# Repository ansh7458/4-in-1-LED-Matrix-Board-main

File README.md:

# 🎮 4-in-1 LED Matrix Board

> **Centre for Electronic Design and Technology**  
> Netaji Subhas University of Technology, New Delhi  
> *Date: December 2024*

---

## 📋 Table of Contents
- [Synopsis](#-synopsis)
- [Introduction](#-introduction)
- [System Overview](#-system-overview)
- [Working Modes](#-working-modes)
- [Program Logic](#-program-logic)
- [Inputs & Control](#-inputs--control)
- [Bill of Materials](#-bill-of-materials)

---

## 🎯 Synopsis

A compact and multifunctional **5×7 LED dot matrix system** built around an **Arduino Nano**. It integrates **four interactive modules** into a single educational platform:

- 🔤 **Morse Tutor** — Learn Morse code interactively
- ⏳ **LED Hourglass** — Tilt-controlled sand animation
- 👁️ **Persistence of Vision (POV) Demo** — Visual persistence effect
- 🌡️ **Temperature Display** — Real-time thermistor reading

User interaction is achieved via **buttons**, **tilt switches**, and a **potentiometer**. The system leverages **Timer1 CTC interrupts** for flicker-free LED multiplexing.

## 📖 Introduction

LED matrices are widely used in educational and commercial applications. This project creates a single, compact platform that consolidates multiple mini-projects, enabling learners to explore different aspects of embedded system design:

| Mode | Concept Demonstrated |
|------|---------------------|
| Morse Tutor | Digital output control, timing-based signal generation |
| Hourglass | Tilt-sensor input handling, animation sequencing |
| POV Demo | Persistence-of-vision, real-time potentiometer control |
| Temperature | Analog sensor reading, calculation, text rendering |

## 🔧 System Overview

### Block Diagram

### Pin Assignment (Arduino Nano)

| Pin | Signal | Connected To | Function |
|-----|--------|-------------|----------|
| D2-D8 | R1-R7 | ULN2003 | Row drives for LED matrix |
| D9-D13 | C1-C5 | BC327 transistors | Column drives |
| A1-A3 | BTN1-3 | Push Buttons | Navigation (Next/Prev/Select) |
| A4-A5 | Tilt 1-2 | Tilt Switches | Hourglass orientation |
| A6 | Thermistor | NTC | Temperature sensing |
| A7 | Pot | RV1 | POV speed control |

## 🎮 Working Modes

### 1. 🏠 Home Screen
Menu navigation using three push buttons (Next, Previous, Select). Long press (~5s) on Button 1 returns to home from any mode.

### 2. 🔤 Morse Tutor
Displays Morse code patterns for A–Z on the LED matrix with timing-based dot/dash rendering.

### 3. ⏳ Hourglass
Tilt-controlled sand animation with direction detection. Passive buzzer alerts when timer completes.

### 4. 👁️ POV Demo
Potentiometer controls Timer1 compare register, varying refresh frequency to demonstrate persistence-of-vision effect.

### 5. 🌡️ Temperature Display
NTC thermistor with **Beta parameter model** for temperature calculation, displayed as scrolling digits on the matrix.

## ⚙️ Program Logic

The firmware follows a **cooperative architecture**:
- **Foreground (main loop)**: User input processing, mode logic, display buffer updates
- **Background (Timer1 ISR)**: Column-wise LED multiplexing at high speed for flicker-free display

## 📦 Bill of Materials

| S.No | Component | Value | Qty |
|------|-----------|-------|-----|
| 1 | Arduino Nano | — | 1 |
| 2 | 5×7 LED Matrix | — | 1 |
| 3 | ULN2003 | Darlington Array | 1 |
| 4 | BC327 | PNP Transistor | 5 |
| 5 | Push Buttons | — | 3 |
| 6 | Tilt Switches | — | 2 |
| 7 | NTC Thermistor | 10 kΩ | 1 |
| 8 | Potentiometer | — | 1 |
| 9 | Passive Buzzer | — | 1 |

## 🛠️ Technologies Used

`Arduino (C/C++)` · `KiCad` · `Timer Interrupts (CTC)` · `Embedded Systems` · `PCB Design`

## 👥 Author
- **Ansh Gupta** — NSUT, New Delhi

---
*Centre for Electronic Design and Technology, NSUT, New Delhi*

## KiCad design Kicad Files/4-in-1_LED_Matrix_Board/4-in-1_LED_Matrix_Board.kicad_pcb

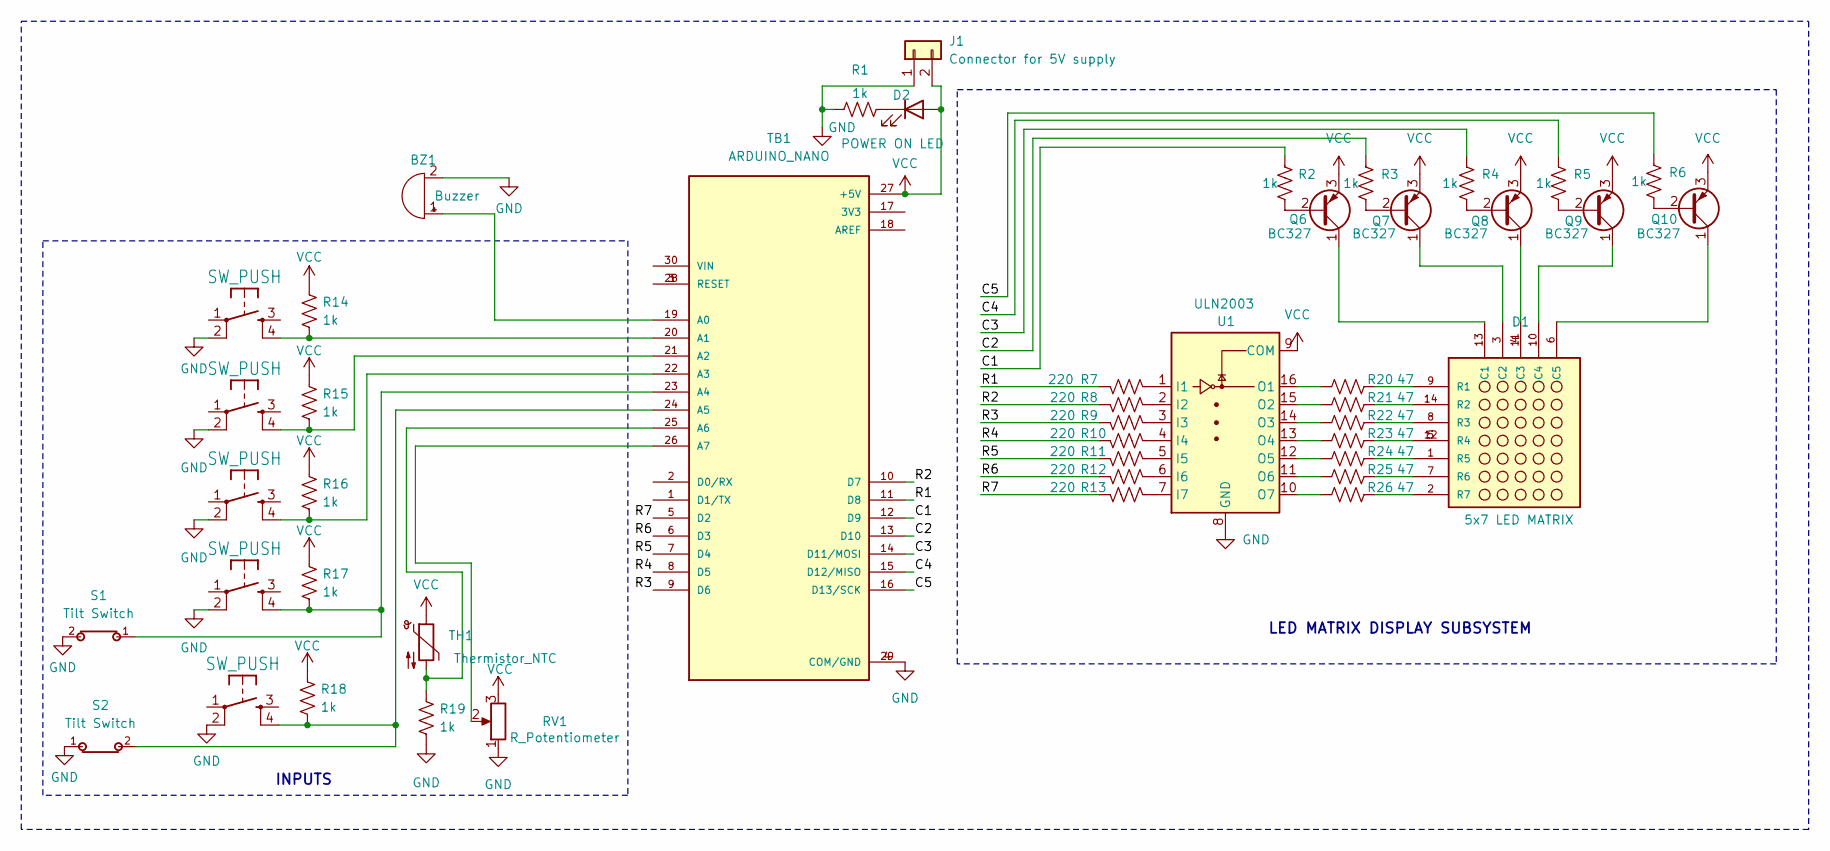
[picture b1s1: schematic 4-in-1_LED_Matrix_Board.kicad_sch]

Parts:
BZ1: Buzzer; XDCR_AT-1438-TWT-R
D1: 5x7 LED MATRIX; LED_TA20-11SRWA; PARTREV V.1A
D2: POWER ON LED; LED_D3.0mm
J1: Connector for 5V supply; JST_EH_B2B-EH-A_1x02_P2.50mm_Vertical
Q6, Q7, Q8, Q9, Q10: BC327; TO-92L_Inline_Wide
R1, R14, R15, R16, R17, R18, R19: 1k; R_Axial_DIN0204_L3.6mm_D1.6mm_P7.62mm_Horizontal
R2, R3, R4, R5, R6: 1k; R_Axial_DIN0207_L6.3mm_D2.5mm_P10.16mm_Horizontal
R7, R8, R9, R10, R11, R12, R13: 220; R_Axial_DIN0204_L3.6mm_D1.6mm_P7.62mm_Horizontal
R20, R21, R22, R23, R24, R25, R26: 47; R_Axial_DIN0204_L3.6mm_D1.6mm_P7.62mm_Horizontal
RV1: R_Potentiometer; RJ9W_2
S1, S2: Tilt Switch; SW-520D
SW1, SW2, SW3, SW4, SW5: SW_PUSH; B3F-40XX
TB1: ARDUINO_NANO; SHIELD_ARDUINO_NANO
TH1: Thermistor_NTC; THERM_GA50K6A1A
U1: ULN2003; DIP-16_W7.62mm

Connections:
/C1: R2.2, TB1.12 (D9)
/C2: R3.1, TB1.13 (D10)
/C3: R4.1, TB1.14 (D11/MOSI)
/C4: R5.1, TB1.15 (D12/MISO)
/C5: R6.1, TB1.16 (D13/SCK)
/R1: R7.1, TB1.11 (D8)
/R2: R8.1, TB1.10 (D7)
/R3: R9.1, TB1.9 (D6)
/R4: R10.1, TB1.8 (D5)
/R5: R11.1, TB1.7 (D4)
/R6: R12.1, TB1.6 (D3)
/R7: R13.1, TB1.5 (D2)
GND: BZ1.2 (-), J1.1, R1.1, R19.1, RV1.1, S1.2, S2.1, SW1.2 (P1), SW2.2 (P1), SW3.2 (P1), SW4.2 (P1), SW5.2 (P1), TB1.4 (COM/GND), TB1.29 (COM/GND), U1.8 (GND)
unnamed: BZ1.1 (+), TB1.19 (A0)
unnamed: D1.13 (C1), Q6.1 (C)
unnamed: D1.3 (C2), Q7.1 (C)
unnamed: D1.10 (C4), Q9.1 (C)
unnamed: D1.6 (C5), Q10.1 (C)
unnamed: D1.9 (R1), R20.1
unnamed: D1.14 (R2), R21.1
unnamed: D1.8 (R3), R22.1
unnamed: D1.5 (R4), D1.12 (R4), R23.1
unnamed: D1.1 (R5), R24.1
unnamed: D1.7 (R6), R25.1
unnamed: D1.2 (R7), R26.1
unnamed: D2.1 (K), R1.2
unnamed: Q6.2 (B), R2.1
unnamed: Q7.2 (B), R3.2
unnamed: Q8.2 (B), R4.2
unnamed: D1.4 (C3), D1.11 (C3), Q8.1 (C)
unnamed: Q9.2 (B), R5.2
unnamed: Q10.2 (B), R6.2
unnamed: R14.1, SW1.4 (S1), TB1.20 (A1)
unnamed: R15.1, SW2.4 (S1), TB1.21 (A2)
unnamed: R16.1, SW3.4 (S1), TB1.22 (A3)
unnamed: R17.1, S1.1, SW4.4 (S1), TB1.23 (A4)
unnamed: R18.1, S2.2, SW5.4 (S1), TB1.24 (A5)
unnamed: R19.2, TB1.25 (A6), TH1.2
unnamed: RV1.2, TB1.26 (A7)
unnamed: TB1.3 (RESET), TB1.28 (RESET)
unnamed: R7.2, U1.1 (I1)
unnamed: R8.2, U1.2 (I2)
unnamed: R9.2, U1.3 (I3)
unnamed: R10.2, U1.4 (I4)
unnamed: R11.2, U1.5 (I5)
unnamed: R12.2, U1.6 (I6)
unnamed: R13.2, U1.7 (I7)
unnamed: R20.2, U1.16 (O1)
unnamed: R21.2, U1.15 (O2)
unnamed: R22.2, U1.14 (O3)
unnamed: R23.2, U1.13 (O4)
unnamed: R24.2, U1.12 (O5)
unnamed: R25.2, U1.11 (O6)
unnamed: R26.2, U1.10 (O7)
VCC: D2.2 (A), J1.2, Q6.3 (E), Q7.3 (E), Q8.3 (E), Q9.3 (E), Q10.3 (E), R14.2, R15.2, R16.2, R17.2, R18.2, RV1.3, TB1.27 (+5V), TH1.1, U1.9 (COM)

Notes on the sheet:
INPUTS
LED MATRIX DISPLAY SUBSYSTEM

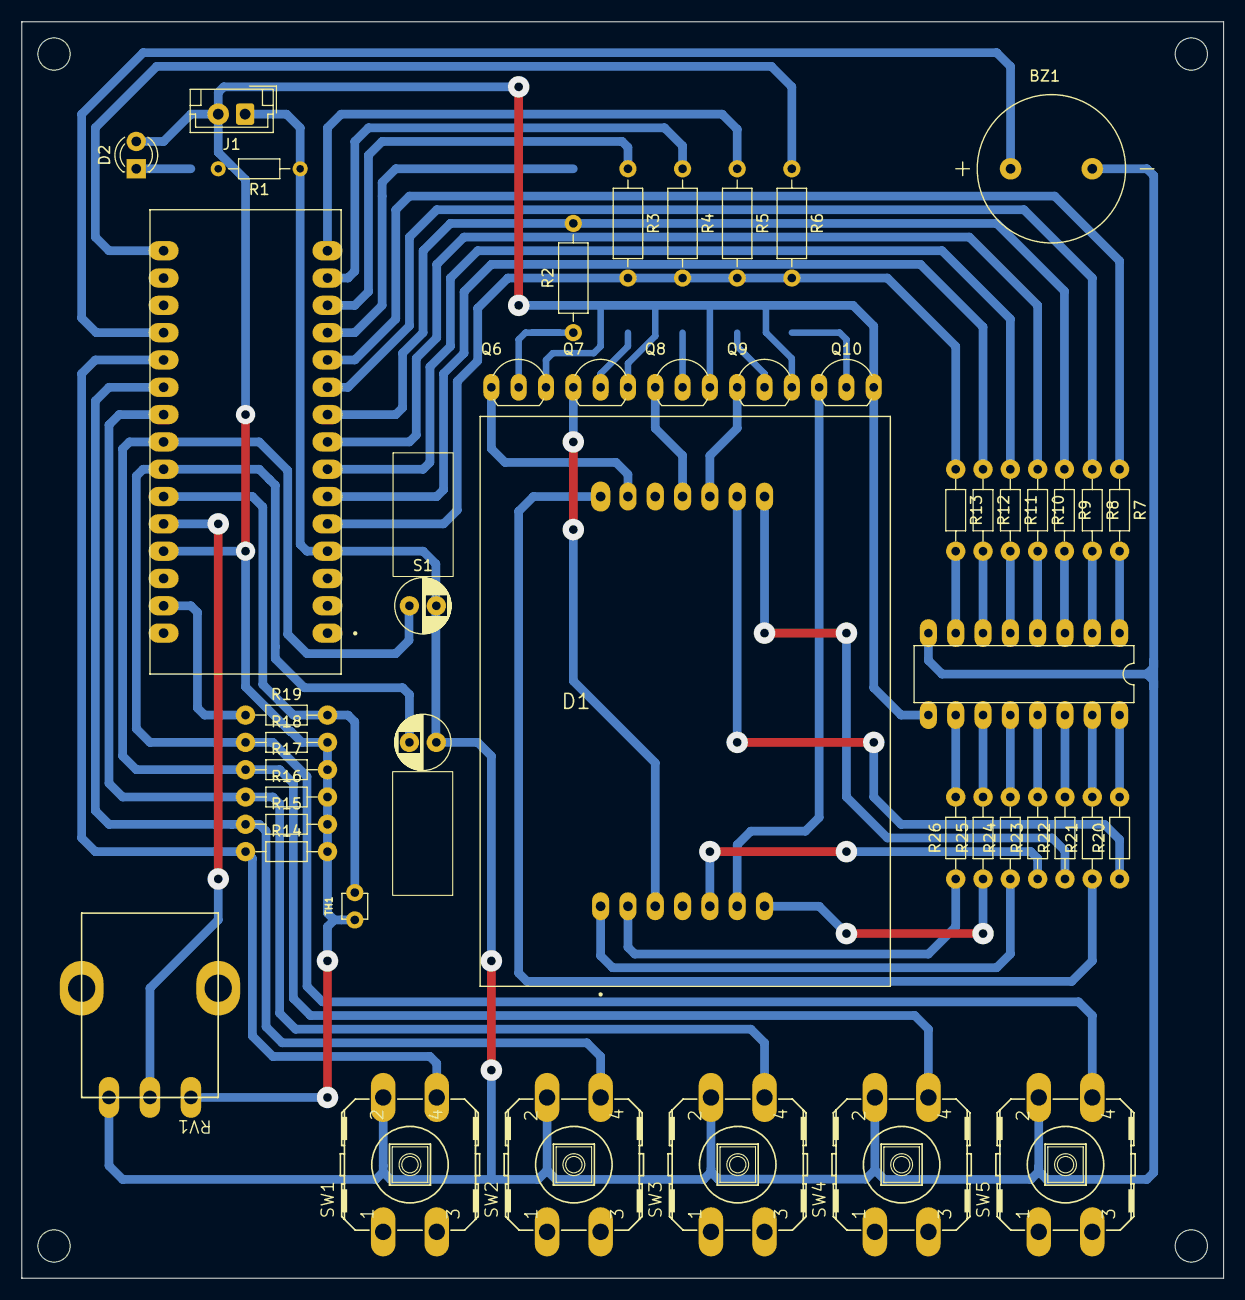
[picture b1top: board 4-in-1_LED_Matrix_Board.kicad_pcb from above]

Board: 2 copper layers, 111.8 x 116.8 mm, 46 parts (0 on the bottom side), 55 nets.
